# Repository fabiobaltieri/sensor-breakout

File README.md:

Sensor Breakout
===============

http://fabiobaltieri.com/2014/06/15/sensor-breakout/

This project is brekout board for prototyping wireless sensors.

Main features:
- ATMega88P microcontroller (can mount up to an ATMetga328)
- nRF24L01+ low power 2.4GHz radio
- On board Lithium battery charger and 3.3V regulator
- Dual mounting option for the USB port (micro B and A)
- Prototype area

License
-------

This program is free software: you can redistribute it and/or modify
it under the terms of the GNU General Public License as published by
the Free Software Foundation, either version 2 of the License, or
(at your option) any later version.

Contents
--------

    COPYING      text version of the GPL
    README       this file
    bootloader/  source directory for bootloader
    firmware/    source directory for main firmware
    hardware/    source directory for the hardware design

Firmware and Bootloader
-----------------------

Building requires an avr-gcc toolchain, in the firmware/ or bootloader/
directory, to build run:

    make

Flashing the firmware on the device requires avrdude and a compatible hardware
programmer. Default configuration is stored at the beginning of the Makefile.
To program with the default configuration, run:

    make flash

Fuses can be configured running:

    make fuses

To program the main firmware from the bootloader, use the command:

    make boot

Hardware
--------

All hardware files (schematic, layout and libraries) are in CadSoft Eagle
format.

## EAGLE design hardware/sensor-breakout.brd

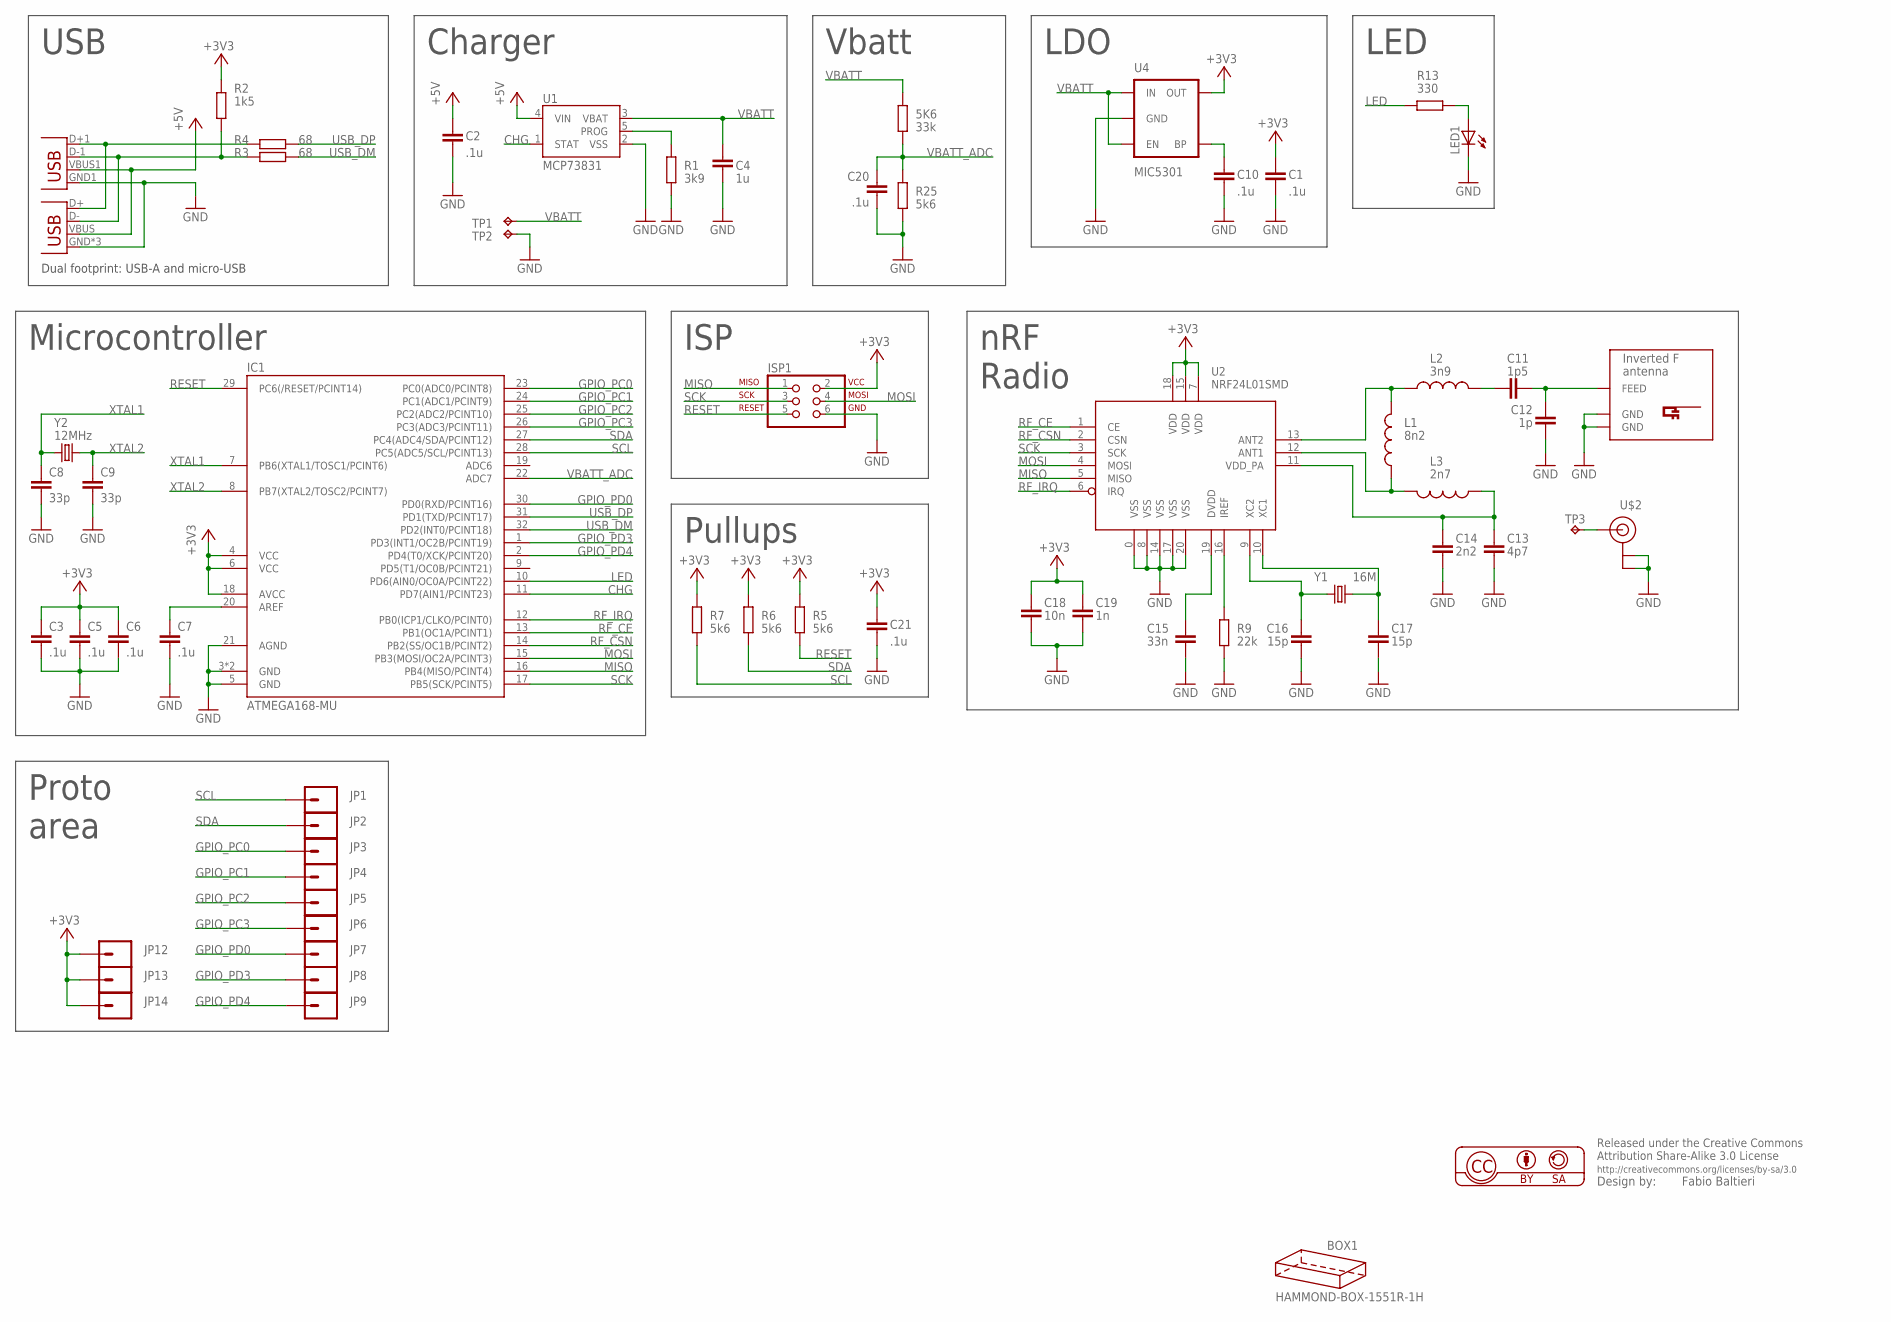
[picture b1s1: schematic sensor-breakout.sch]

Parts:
5K6: 33k; R0603
BOX1: HAMMOND-BOX-1551R-1H; 1551R-1HOLE
C1, C2, C3, C5, C6, C7, C10, C20, C21: .1u; C0603
C4: 1u; C0603
C8, C9: 33p; C0603
C11: 1p5; C0603
C12: 1p; C0603
C13: 4p7; C0603
C14: 2n2; C0603
C15: 33n; C0603
C16, C17: 15p; C0603
C18: 10n; C0603
C19: 1n; C0603
IC1: ATMEGA168-MU; MLF32-TH
ISP1: ISP-AVR910PTH; 2X03
JP1, JP2, JP3, JP4, JP5, JP6, JP7, JP8, JP9, JP12, JP13, JP14: M01NOSILK-KIT; 1X01NS-KIT
JP10: USB-MICROB
JP11: USBA-SMD-MALE; USB-A-SMT-MALE
L1: 8n2; 0603
L2: 3n9; 0603
L3: 2n7; 0603
LED1: LEDSML0805; SML0805
R1: 3k9; R0603
R2: 1k5; R0603
R3, R4: 68; R0603
R5, R6, R7, R25: 5k6; R0603
R9: 22k; R0603
R13: 330; R0603
TP1, TP2: TPTP12R; TP12R
TP3: TPTP08SQ; TP08SQ
U1: MCP73831; SOT23-5
U2: NRF24L01SMD; QFN20
U4: MIC5301; SOT23-5
U$1: INVERTED_F_ANTENNA-2; DN007-2
U$2: U.FL
Y1: 16M; CRYSTAL-SMD-5X3
Y2: 12MHz; CRYSTAL-SMD-5X3

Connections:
+3V3: C1.1, C3.1, C5.1, C6.1, C18.1, C19.1, C21.1, IC1.4 (VCC), IC1.6 (VCC), IC1.18 (AVCC), ISP1.2, JP12.1, JP13.1, JP14.1, R2.2, R5.1, R6.1, R7.1, U2.7 (VDD), U2.15 (VDD), U2.18 (VDD), U4.5 (OUT)
+5V: C2.1, JP10.VBUS, JP11.VBUS1 (VBUS), U1.4 (VIN)
CHG: IC1.11 (PD7(AIN1/PCINT23)), U1.1 (STAT)
GND: C1.2, C2.2, C3.2, C4.2, C5.2, C6.2, C7.2, C8.2, C9.2, C10.2, C12.2, C13.2, C14.2, C15.2, C16.2, C17.2, C18.2, C19.2, C20.2, C21.2, IC1.3 (GND), IC1.5 (GND), IC1.21 (AGND), IC1.TH (GND), ISP1.6, JP10.GND, JP10.MT1 (GND), JP10.MT2 (GND), JP11.GND1 (GND), LED1.C, R1.2, R9.2, R25.2, TP2.TP, U1.2 (VSS), U2.0 (VSS), U2.8 (VSS), U2.14 (VSS), U2.17 (VSS), U2.20 (VSS), U4.2 (GND), U$1.GND, U$1.GND@1 (GND), U$2.P$1 (GND), U$2.P$2 (GND)
GPIO_PC0: IC1.23 (PC0(ADC0/PCINT8)), JP3.1
GPIO_PC1: IC1.24 (PC1(ADC1/PCINT9)), JP4.1
GPIO_PC2: IC1.25 (PC2(ADC2/PCINT10)), JP5.1
GPIO_PC3: IC1.26 (PC3(ADC3/PCINT11)), JP6.1
GPIO_PD0: IC1.30 (PD0(RXD/PCINT16)), JP7.1
GPIO_PD3: IC1.1 (PD3(INT1/OC2B/PCINT19)), JP8.1
GPIO_PD4: IC1.2 (PD4(T0/XCK/PCINT20)), JP9.1
LED: IC1.10 (PD6(AIN0/OC0A/PCINT22)), R13.2
MISO: IC1.16 (PB4(MISO/PCINT4)), ISP1.1, U2.5 (MISO)
MOSI: IC1.15 (PB3(MOSI/OC2A/PCINT3)), ISP1.4, U2.4 (MOSI)
unnamed: JP10.D+, JP11.D+1 (D+), R4.2
unnamed: C7.1, IC1.20 (AREF)
unnamed: LED1.A, R13.1
unnamed: R1.1, U1.5 (PROG)
unnamed: L1.2, L3.2, U2.12 (ANT1)
unnamed: L1.1, L2.1, U2.13 (ANT2)
unnamed: JP10.D-, JP11.D-1 (D-), R2.1, R3.2
unnamed: C10.1, U4.4 (BP)
unnamed: C11.1, L2.2
unnamed: C11.2, C12.1, U$1.FEED
unnamed: C13.1, C14.1, L3.1, U2.11 (VDD_PA)
unnamed: C15.1, U2.19 (DVDD)
unnamed: R9.1, U2.16 (IREF)
unnamed: C17.1, U2.10 (XC1), Y1.3 (2)
unnamed: C16.1, U2.9 (XC2), Y1.1
unnamed: TP3.TP, U$2.P$3 (SIGNAL)
RESET: IC1.29 (PC6(/RESET/PCINT14)), ISP1.5, R5.2
RF_CE: IC1.13 (PB1(OC1A/PCINT1)), U2.1 (CE)
RF_CSN: IC1.14 (PB2(SS/OC1B/PCINT2)), U2.2 (CSN)
RF_IRQ: IC1.12 (PB0(ICP1/CLKO/PCINT0)), U2.6 (IRQ)
SCK: IC1.17 (PB5(SCK/PCINT5)), ISP1.3, U2.3 (SCK)
SCL: IC1.28 (PC5(ADC5/SCL/PCINT13)), JP1.1, R7.2
SDA: IC1.27 (PC4(ADC4/SDA/PCINT12)), JP2.1, R6.2
USB_DM: IC1.32 (PD2(INT0/PCINT18)), R3.1
USB_DP: IC1.31 (PD1(TXD/PCINT17)), R4.1
VBATT: 5K6.1, C4.1, TP1.TP, U1.3 (VBAT), U4.1 (IN), U4.3 (EN)
VBATT_ADC: 5K6.2, C20.1, IC1.22 (ADC7), R25.1
XTAL1: C8.1, IC1.7 (PB6(XTAL1/TOSC1/PCINT6)), Y2.1
XTAL2: C9.1, IC1.8 (PB7(XTAL2/TOSC2/PCINT7)), Y2.3 (2)

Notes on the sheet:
ISP
LED
nRF
Charger
Radio
LDO
Microcontroller
USB
Pullups
Vbatt
Dual footprint: USB-A and micro-USB
Proto area

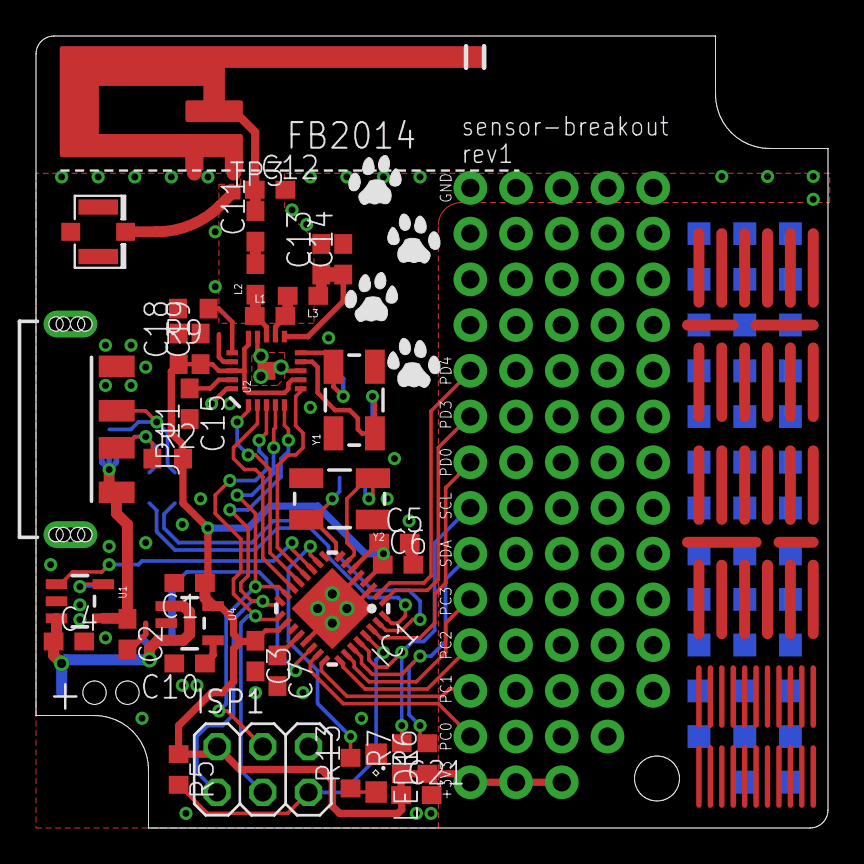
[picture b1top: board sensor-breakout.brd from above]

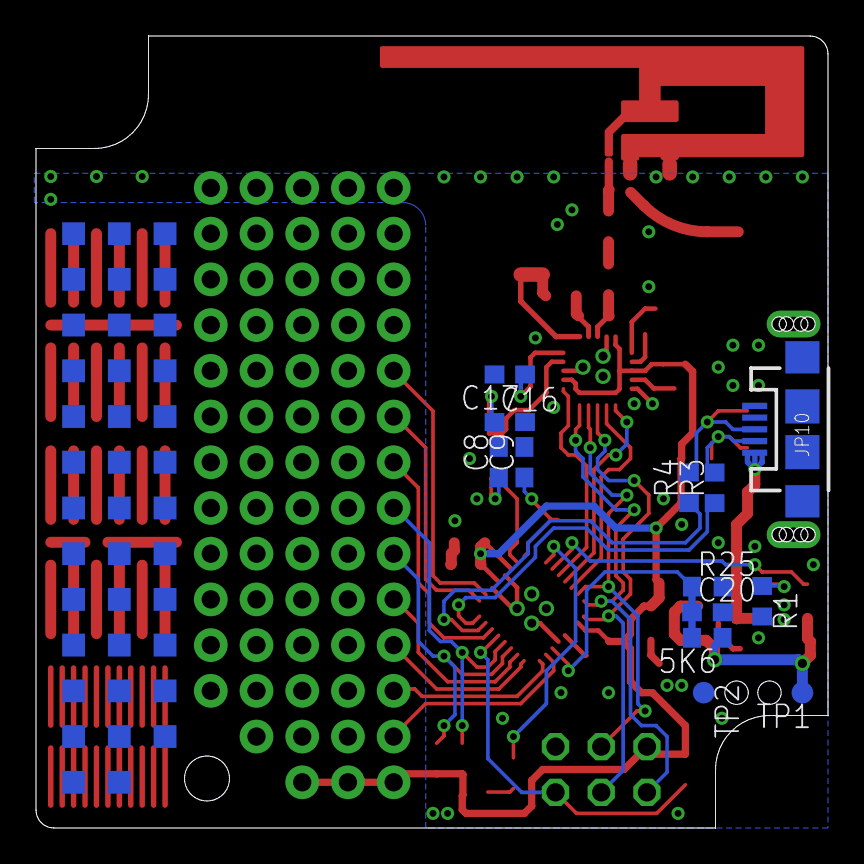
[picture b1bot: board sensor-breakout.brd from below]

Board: 2 copper layers, 44.0 x 44.0 mm, 67 parts (13 on the bottom side), 43 nets.

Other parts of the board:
U$3, U$5: CAT-R
U$4, U$6: CAT-L

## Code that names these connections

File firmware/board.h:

void reset_cpu(void);

/* LED */
#define LED_PORT	PORTD
#define LED_DDR		DDRD
#define LED		PD6

#define led_on()	LED_PORT |=  _BV(LED)
#define led_off()	LED_PORT &= ~_BV(LED)
#define led_toggle()	LED_PORT ^=  _BV(LED)

#define led_init()				\
	do {					\
		LED_DDR |= _BV(LED);		\
		LED_DDR |= _BV(LED);		\
	} while (0);

/* SPI */
#define SPI_DDR  DDRB
#define SPI_PORT PORTB
#define SPI_SS   PB2
#define SPI_SCK  PB5
#define SPI_MOSI PB3
#define SPI_MISO PB4

/* nRF24L01+ SPI */
#define NRF_DDR  DDRB
#define NRF_PORT PORTB
#define NRF_CS   SPI_SS
#define NRF_CE   PB1

#define nrf_cs_h() (NRF_PORT |=  _BV(NRF_CS))
#define nrf_cs_l() (NRF_PORT &= ~_BV(NRF_CS))
#define nrf_ce_h() (NRF_PORT |=  _BV(NRF_CE))
#define nrf_ce_l() (NRF_PORT &= ~_BV(NRF_CE))

#define NRF_PCMSK PCMSK0
#define NRF_PCINT PCINT0

/* Charger */
#define CHG_PORT        PORTD
#define CHG_PIN         PIND
#define CHG             PD7

#define chg_init()      do { CHG_PORT |= _BV(CHG); } while (0)
#define is_charging()   (!(CHG_PIN & _BV(CHG)))

/* ADC */
#define ADC_VREF_mV (1100 / 4)
#define ADC_VREF_BITS (1024 / 4)
#define ADC_VBATT 7

#define VBAT_L (56) /* divider low */
#define VBAT_H (330 + VBAT_L) /* divider high */

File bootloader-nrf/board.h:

void reset_cpu(void);

/* LED */
#define LED_PORT	PORTC
#define LED_DDR		DDRC
#define LED		PC6

#define led_on()	LED_PORT |=  _BV(LED)
#define led_off()	LED_PORT &= ~_BV(LED)
#define led_toggle()	LED_PORT ^=  _BV(LED)

#define led_init()				\
	do {					\
		LED_DDR |= _BV(LED);		\
		LED_DDR |= _BV(LED);		\
	} while (0);

/* SPI */
#define SPI_DDR  DDRB
#define SPI_PORT PORTB
#define SPI_SS   PB0
#define SPI_SCK  PB1
#define SPI_MOSI PB2
#define SPI_MISO PB3

/* nRF24L01+ SPI */
#define NRF_DDR  DDRB
#define NRF_PORT PORTB
#define NRF_CS   SPI_SS
#define NRF_CE   PB4

#define nrf_cs_h() (NRF_PORT |=  _BV(NRF_CS))
#define nrf_cs_l() (NRF_PORT &= ~_BV(NRF_CS))
#define nrf_ce_h() (NRF_PORT |=  _BV(NRF_CE))
#define nrf_ce_l() (NRF_PORT &= ~_BV(NRF_CE))

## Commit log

2013-11-24 hw: rc0
2013-11-24 hw: rc1
2013-11-24 hw: rc2
2013-12-09 add bootloader
2013-12-15 hw: add pdf schematic
2013-12-15 add gitignore
2013-12-15 fw: add firmware skeleton
2013-12-26 bootloader-nrf: add first working version (tested on atmega32u2)
2014-01-01 bl: remove comment from fuse (avrdude gets confused)
2014-01-01 bl: swap usb pins
2014-01-01 move nrf_frames.h in main firmware directory
2014-01-01 fw: add spi pins to board definitions
2014-01-01 fw: add spi and nrf files
2014-01-01 fw: add ambient type in nrf_frames.h
2014-01-01 fw: add basic send code
2014-01-01 nrf_frames: add ambient field in msg union
2014-01-01 fw: add charger detection and battery voltage measurement
2014-01-01 fw: add adc code
2014-01-01 fw: add board id reding from eeprom
2014-01-02 hw: update values
2014-01-14 fw: wait longer for adc to stabilize
2014-01-14 fw: add ref option for adc_get
2014-01-14 fw: nrf: put radio in powerdown after tx
2014-01-15 fw: call nrf_poll on radio interrupt
2014-01-15 fw: use sleep mode and watchdog for periodic wakeup
2014-01-20 fw: set sleep mod to power down
2014-05-05 hw: rev1, moved battery pads on bottom
2014-06-15 add README and COPYING
2014-07-17 hw: fix ldo part number

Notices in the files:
parts and their libraries:
SparkFun: Licensing: CC v3.0 Share-Alike You are welcome to use this library for commercial purposes.
balto: Released under the Creative Commons
balto: http://creativecommons.org/licenses/by-sa/3.0
